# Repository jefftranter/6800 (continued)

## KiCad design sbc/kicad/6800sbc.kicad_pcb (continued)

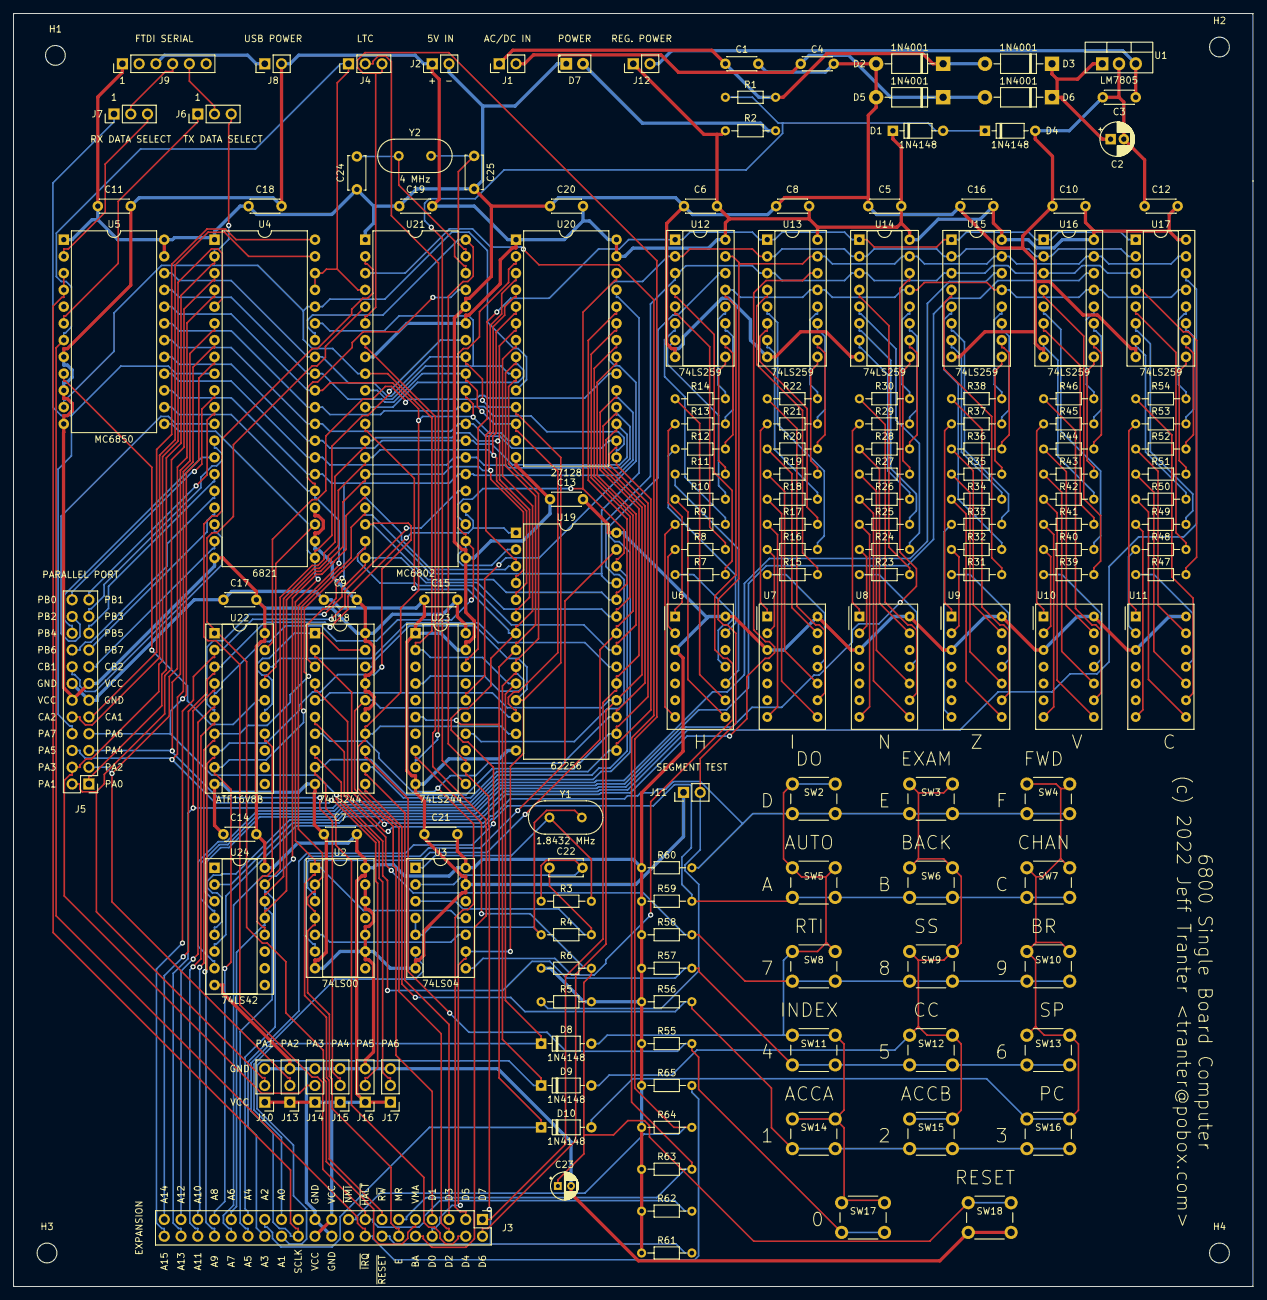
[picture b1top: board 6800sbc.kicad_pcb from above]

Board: 2 copper layers, 188.0 x 193.0 mm, 164 parts (0 on the bottom side), 200 nets.

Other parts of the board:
H1, H2, H3, H4: MountingHole_3mm

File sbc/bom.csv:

Reference, Quantity, Value, Footprint, Datasheet
C2 ,1,"1000uF","","~"
C22 ,1,"1nF","","~"
C23 ,1,"100uF","","~"
C25 C24 ,2,"30 pF","","~"
C5 C1 C6 C7 C8 C9 C4 C10 C11 C12 C13 C14 C15 C16 C17 C18 C19 C20 C21 C3 ,20,"0.1uF","","~"
D2 D1 D5 D6 D7 ,5,"1N4148","Diode_THT:D_DO-35_SOD27_P7.62mm_Horizontal","http://www.microsemi.com/document-portal/doc_view/11580-lds-0239"
D3 ,1,"1N4001 X4","","~"
D4 J1 ,2,"POWER","","~"
J2 ,1,"5V POWER","","~"
J5 ,1,"LTC","","~"
J6 ,1,"EXPANSION","","~"
J7 ,1,"PARALLEL PORT","","~"
J8 ,1,"FTDI SERIAL","","~"
J9 ,1,"USB POWER","","~"
R1 ,1,"8K2","","~"
R2 ,1,"330","","~"
R3 R4 ,2,"2K2","","~"
R53 ,1,"4K7","","~"
R54 ,1,"3K","","~"
RN1 ,1,"8K2","Resistor_THT:R_Array_SIP7","http://www.vishay.com/docs/31509/csc.pdf"
RN2 ,1,"3K","Resistor_THT:R_Array_SIP9","http://www.vishay.com/docs/31509/csc.pdf"
RN3 RN4 RN5 RN6 RN7 RN8 ,6,"470","","~"
SW1 ,1,""D"","","~"
SW10 ,1,""4"","","~"
SW11 ,1,""5"","","~"
SW12 ,1,""6"","","~"
SW13 ,1,""1"","","~"
SW14 ,1,""2"","","~"
SW15 ,1,""3"","","~"
SW16 ,1,""0"","","~"
SW17 ,1,""RESET"","","~"
SW18 ,1,"SEGMENT TEST","","~"
SW2 ,1,""E"","","~"
SW3 ,1,""F"","","~"
SW4 ,1,""A"","","~"
SW5 ,1,""B"","","~"
SW6 ,1,""C"","","~"
SW7 ,1,""7"","","~"
SW8 ,1,""8"","","~"
SW9 ,1,""9"","","~"
U1 ,1,"LM7805","Package_TO_SOT_THT:TO-220-3_Vertical","http://www.fairchildsemi.com/ds/LM/LM7805.pdf"
U11 U12 U13 U14 U15 U16 ,6,"74LS259","","http://www.ti.com/lit/gpn/sn74LS259"
U17 U23 ,2,"74LS244","","http://www.ti.com/lit/gpn/sn74LS244"
U18 ,1,"62256 RAM","Package_DIP:DIP-28_W15.24mm","https://ecee.colorado.edu/~mcclurel/Cypress_SRAM_CY62256.pdf"
U19 ,1,"27128","Package_DIP:DIP-28_W15.24mm","http://eeshop.unl.edu/pdf/27128.pdf"
U2 ,1,"6821","Package_DIP:DIP-40_W15.24mm","http://pdf.datasheetcatalog.com/datasheet/motorola/6821.pdf"
U20 ,1,"MC6802","Package_DIP:DIP-40_W15.24mm","https://www.jameco.com/Jameco/Products/ProdDS/43502.pdf"
U22 ,1,"ATF16V8B","",""
U24 ,1,"74LS42","","http://www.ti.com/lit/gpn/sn74LS42"
U25 ,1,"74LS00","","http://www.ti.com/lit/gpn/sn74ls00"
U3 ,1,"MC6850","Package_DIP:DIP-40_W15.24mm","http://pdf.datasheetcatalog.com/datasheet/motorola/MC6850.pdf"
U4 ,1,"74LS04","","http://www.ti.com/lit/gpn/sn74LS04"
U5 U6 U7 U8 U9 U10 ,6,"MAN71A","Display_7Segment:MAN71A","https://www.digchip.com/datasheets/parts/datasheet/161/MAN36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"
Y1 ,1,"1.8432 MHz","","~"
Y2 ,1,"3.579545 kHz","","~"

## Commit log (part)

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2018-07-09 Check in start of new project.
2018-07-11 Enter more code.
2018-07-14 Almost there.
2018-07-14 Fixing typos.
2018-07-14 Appears to be generating correct code now.
2018-07-14 Add some comments.
2018-07-16 Fix an error. Output now matches Heathkit ROMs.
2018-07-21 Check in assembled output files.
2018-07-22 Start entering ETA-3400 code.
2018-07-22 All code entered, still some errors to resolve.
2018-07-22 Assembles now, still some differences in generated output.
2018-07-22 Memory addresses are correct, did not verify against original ROM yet.
2018-07-23 Fix assembly warnings.
2018-07-23 Minor fixes. Is generating some incorrect code.
2018-07-23 Workaround for assembler bug.
2018-07-23 Add code in ROM but missing from source code.
2018-07-23 Minor improvement.
2018-07-23 Code now matches ROMS and has reverse engineered source for undocumented patches.
2018-07-23 Fill unused locations with FF.
2018-07-24 Check in Tiny BASIC ROM source.
2018-07-24 Remove generated comments.
2018-07-24 Minor cleanup. Check in generated files.
2018-07-24 Updated readme for Tiny BASIC.
2018-07-26 Fix some typos.
2018-07-29 Add first sample program.
2018-07-29 Add second sample program.
2018-07-29 Add third sample program.
2018-07-29 Fix some errors.
2018-07-29 Add fourth sample program.
2018-07-29 Add fifth sample program.
2018-07-29 Add sixth sample program.
2018-07-29 Add ET-3400A version of code.
2018-07-29 Enter seventh example. Check in listings and run files.
2018-07-30 Minor changes.
2018-07-31 Add sample program.
2018-07-31 Add comments from Heathkit ETA-3400 manual.
2018-08-01 Reverse engineering more of the source, based on 6502 version.
2018-08-01 Reverse engineering more of the source.
2018-08-01 Add more reverse engineered code.
2018-08-06 Check in MikBug source.
2018-08-06 Adjust addresses for ET-3400 and ETA-3400 (untested).
2018-08-06 Convert some spaces to tabs.
2018-08-07 Switch to version that appears to be original from Motorola.
2018-08-07 Use start address to set up correct vectors.
2018-08-16 Add another example of my own.
2018-08-18 Add notes on using IRQ instead of NMI.
2018-08-18 Update some comments and remove whitespace.
2018-08-18 Fix page width and length. Add first version of new program.
2018-08-19 Bug fixes.
2018-08-19 Add 24-hour support.
2018-08-19 Prompt user for initial time.
2018-08-20 Add instructions on 2716 EPROM modification.
2018-09-12 Check in first few example programs.
2018-09-13 Check in more few example programs.
2019-02-22 Fix typo.
2019-02-22 Change hardcoded addresses to labels.
2019-03-01 Start entering MONDEB source code.
2019-03-01 Entering more code.
2019-03-03 Entering more code, and boy are my arms tired!
2019-03-03 Finished initial entering of code.
2019-03-03 Now assembles, but likely still has some errors.
2019-03-03 Fixes.
2019-03-03 Update readme.
2019-03-03 Fix.
2019-03-04 Check in run file in listing.
2019-03-04 Make some fixes.
2019-03-05 Bug fix.
2019-03-07 Fixed more errors. Output is now identical to book.
2021-12-24 Change origin for example to match manual. Remove statement that I do not own an ETA-3400 as I have on (a modern replica).
2021-12-31 Remove MikBug as it is not feasible to port due to hardware differences with Motorola 6800D2 board.
2022-01-13 Initial commit of files for Single Board Computer design (still a work in progress).
2022-01-14 Check in port of monitor (untested).
2022-01-15 Circuit updates.
2022-01-15 Fix error in memory map.
2022-01-16 Add ports of serial monitor and Tiny Basic (untested).
2022-01-16 Add make file rules to generate binary file.
2022-01-18 Add original versions of mikbug and minibug.
2022-01-18 Porting to crasm assembler.
2022-01-18 Foundline that caused assembler to crash.
2022-01-18 Porting MiniBug and MikBug and integrating into EPROM.
2022-01-20 Check in source for MS Basic (still a work in progress.)
2022-01-20 Add TODO items.
2022-01-21 Fixed for labels.
2022-01-21 Removing labels.
2022-01-22 Updates, start of PCB.
2022-01-22 Remove BOM CSV file as it can be generated from Kicad.
2022-01-24 Updates to PCB design.
2022-02-06 Correct error.
2022-02-06 Some fixes based on prototyping work.
2022-02-06 Fx typo. Use external RAM. Add EPPROM programmer commands to make file.
2022-02-07 Fix error in LED wiring.
2022-02-07 Minor updates.
2022-02-09 Fix error.
2022-02-10 Various updates.
2022-02-12 Getting close to ready to order PCBs. Check in all files.
2022-02-13 Optimizing board layout.
2022-02-13 Add some info on connectors and jumpers.
2022-03-04 Some corrections to schematic and added to documentation.
2022-03-04 Update PCB elayout and Gerber files for rev 1.0PCB.
2022-03-04 Update schematic.
2022-03-04 Check in initial code (not yet ported to SBC).
2022-03-06 Bug fix. Last chance was incorrect.
2022-03-06 Remove extra whitespace.
2022-03-09 First working version of Fantom II with ACIA.
2022-03-09 Fix for some bad characters in output.
2022-03-09 Fixes for PUNCH command.
2022-03-10 Fix STEP command by aligning interrupt vectors with both monitors.
2022-03-12 Documentation updates.
2022-03-12 Bug fix. Tiny basic is now workking. Adding more comments from original source code.
2022-03-12 Suppress nulls in output.
2022-03-12 Add more comments from original source code.
2022-03-13 Add to do list.
2022-03-15 Add example program.
2022-03-19 Start of disassembler.
2022-03-20 Working on disassembler.
2022-03-21 Formatting fixes.
2022-03-22 Bug fix, code cleanup.
2022-03-22 Add support for entering diasassembly address.
2022-03-22 Integrate disassembler into ROM.
2022-03-22 Mention disassembler in README file.
2022-03-23 Basic porting.
2022-03-23 Perform ACIA and stack initialization so disassembler can be run standalone.
2022-03-23 Update README for disassembler.
2022-03-23 Check in original version of TSC Micro Basic source code.
2022-03-23 Porting to SBC. Working, but not reliably.
2022-03-24 Initialize ACIA and stack at startup.
2022-03-26 Add more info on TSC Basic.
2022-03-26 Check in binaries for ROM.
2022-03-26 Integrate TSC Basic into ROM.
2022-03-26 Check in latest ROM image files.
2022-03-30 Add ROM image with Microsoft Basic.
2022-03-30 Add some info on Basic.
2022-03-30 Add ROM image files.
2022-03-30 Add link to Altair Basic manual.
2022-03-31 Fix some typos in README file.
2022-04-02 First attempt at DS1216 program.
2022-04-02 Improve code.
2022-04-03 Add code for writing to clock registers.
2022-04-04 Rename MicroBas to tscbasic to avoid confusion with another Micro Basic.
2022-04-05 Add Robert Uiterwyk's Micro Basic.
2022-04-05 Porting to SBC.
2022-04-06 Some whitespace formatting cleanup.
2022-04-07 Revert bug fixes lists at original website for microbasic as they introduced bugs. Seems to we working now.
2022-04-07 Add more documentation and build it by default.
2022-04-08 Add more comments. Fixed bug with REM command.
2022-04-10 Start of DS1302 code example.
2022-04-10 Starting to implement code.
2022-04-10 Debugging.
2022-04-10 Add more functionality.
2022-04-10 Reading clock is now working.
2022-04-11 Implement write function.
2022-04-11 Code cleanup.
2022-04-11 Set time as well as date.
2022-04-11 Add some more comments. Initialize stack.
2022-04-11 Add note on port A.
2022-05-31 Clarify some commands.
2022-10-29 Add note on the cross-assembler the code was written for.
2023-03-12 Fix small typo.
2024-01-22 Update EPROMMod.txt
    Single typo.
2024-04-14 Change C2 to 100uF.
2025-06-24 Add license info.
